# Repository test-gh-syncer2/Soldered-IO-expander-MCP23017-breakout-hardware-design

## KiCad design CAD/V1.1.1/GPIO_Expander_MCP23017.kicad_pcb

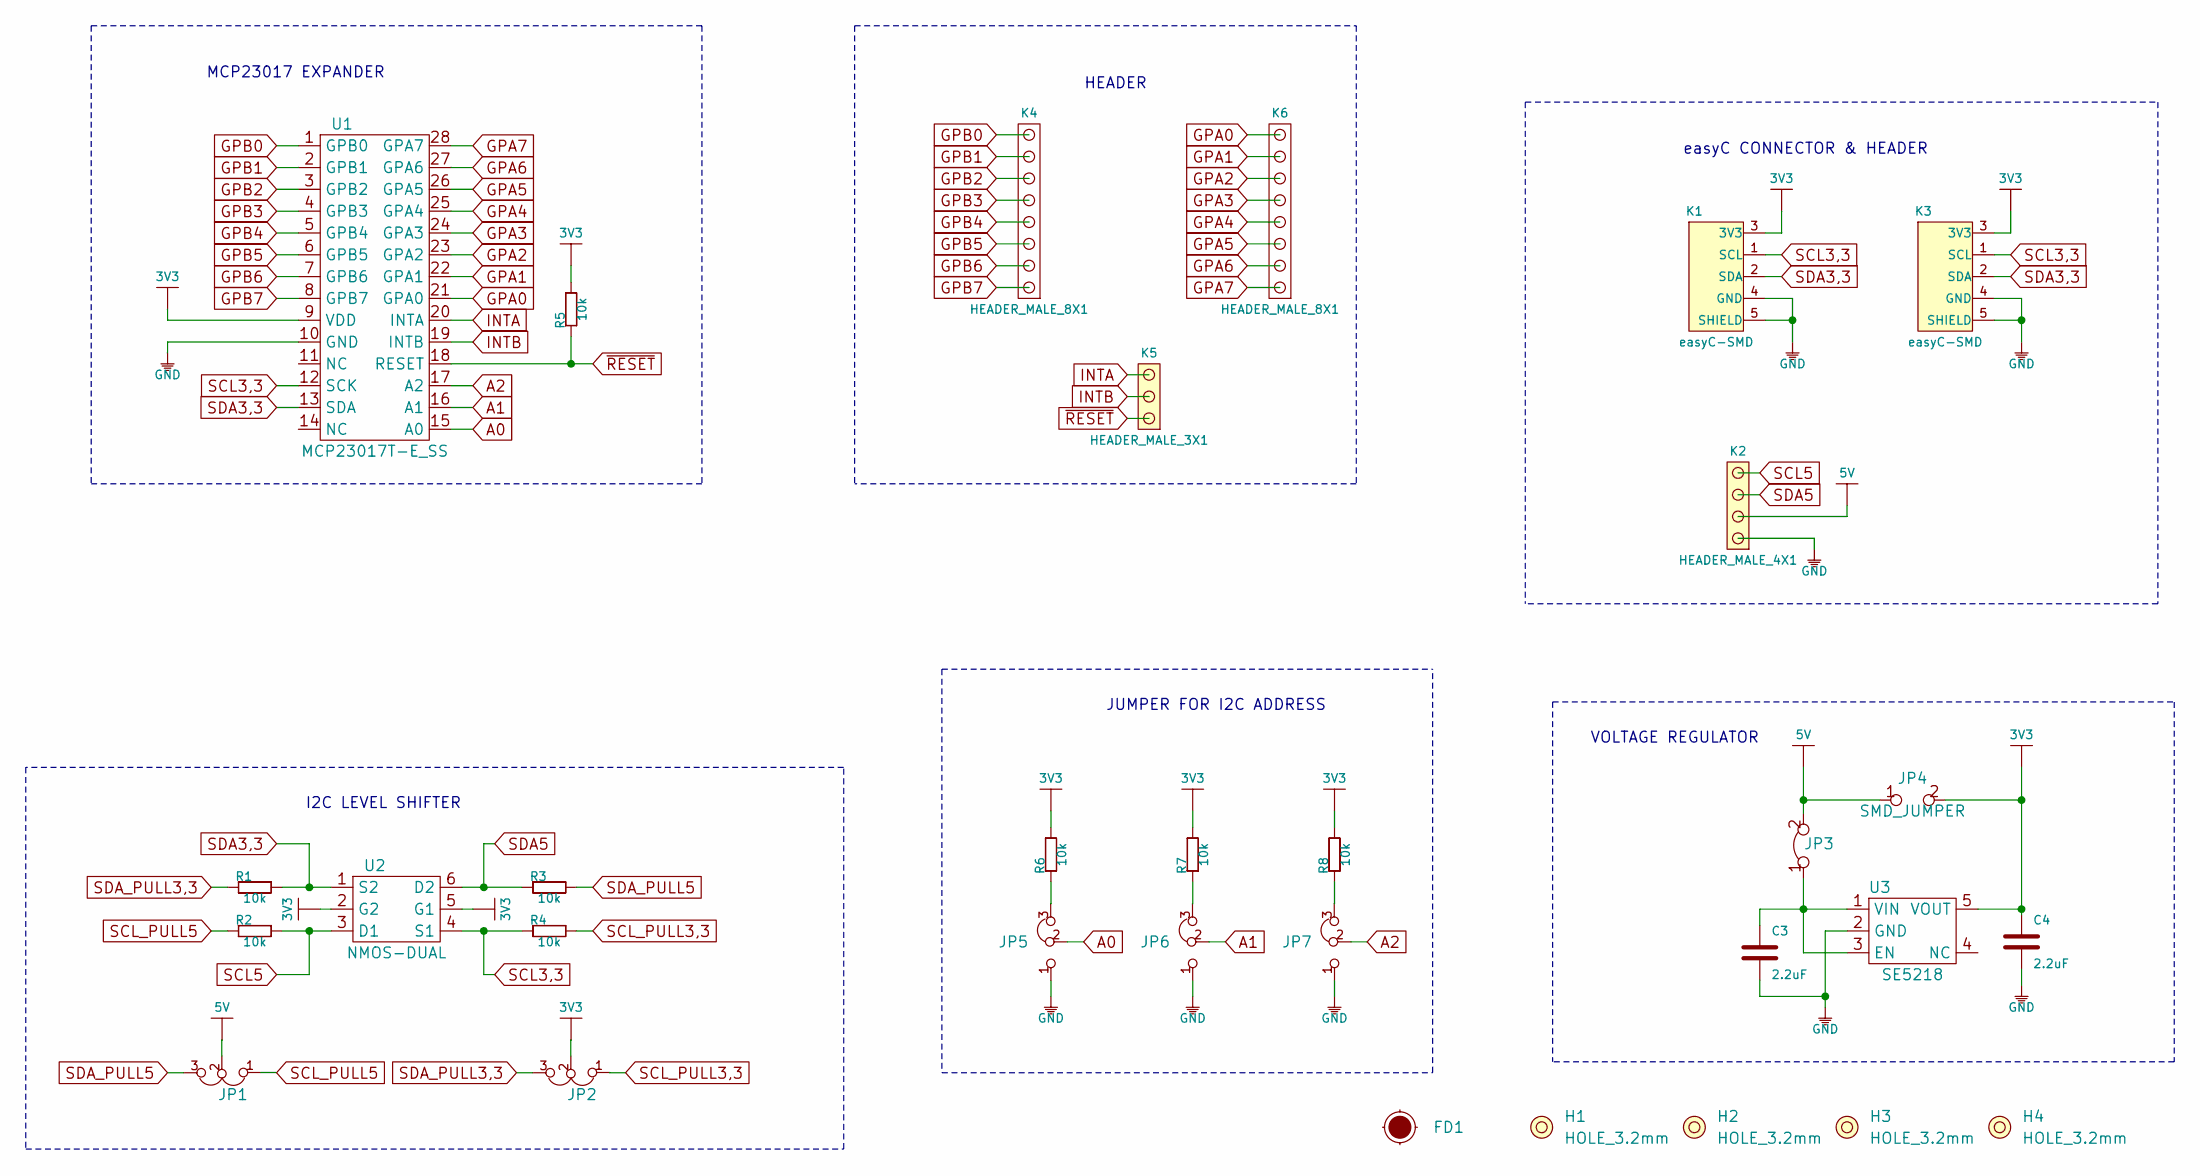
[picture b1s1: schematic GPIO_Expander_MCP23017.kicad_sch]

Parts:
C3, C4: 2.2uF; 0603C
FD1: Fiducial_Stencil; FIDUCIAL_1MM_PASTE
H1, H2, H3, H4: HOLE_3.2mm
JP1, JP2: SMD_JUMPER_3_PAD_TRACE
JP3: SMD-JUMPER-CONNECTED_TRACE_SLODERMASK
JP4: SMD_JUMPER
JP5, JP6, JP7: SMD_JUMPER_3_PAD_CONNECTED_RIGHT
K1, K3: easyC-SMD; easyC-connector
K2: HEADER_MALE_4X1
K4, K6: HEADER_MALE_8X1
K5: HEADER_MALE_3X1
R1, R2, R3, R4, R5, R6, R7, R8: 10k; 0603R
U1: MCP23017T-E_SS; MCP23017
U2: NMOS-DUAL; SOT-363
U3: SE5218; SOT-23-5

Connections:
3V3: C4.2, JP2.2, JP4.2, K1.3 (3V3), K3.3 (3V3), R5.2, R6.2, R7.2, R8.2, U1.9 (VDD), U2.2 (G2), U2.5 (G1), U3.5 (VOUT)
5V: JP1.2, JP3.2, JP4.1, K2.2
A0: JP5.2, U1.15 (A0)
A1: JP6.2, U1.16 (A1)
A2: JP7.2, U1.17 (A2)
GND: C3.1, C4.1, JP5.1, JP6.1, JP7.1, K1.4 (GND), K1.5 (SHIELD), K2.1, K3.4 (GND), K3.5 (SHIELD), U1.10 (GND), U3.2 (GND)
GPA0: K6.8, U1.21 (GPA0)
GPA1: K6.7, U1.22 (GPA1)
GPA2: K6.6, U1.23 (GPA2)
GPA3: K6.5, U1.24 (GPA3)
GPA4: K6.4, U1.25 (GPA4)
GPA5: K6.3, U1.26 (GPA5)
GPA6: K6.2, U1.27 (GPA6)
GPA7: K6.1, U1.28 (GPA7)
GPB0: K4.8, U1.1 (GPB0)
GPB1: K4.7, U1.2 (GPB1)
GPB2: K4.6, U1.3 (GPB2)
GPB3: K4.5, U1.4 (GPB3)
GPB4: K4.4, U1.5 (GPB4)
GPB5: K4.3, U1.6 (GPB5)
GPB6: K4.2, U1.7 (GPB6)
GPB7: K4.1, U1.8 (GPB7)
INTA: K5.3, U1.20 (INTA)
INTB: K5.2, U1.19 (INTB)
unnamed: C3.2, JP3.1, U3.1 (VIN), U3.3 (EN)
unnamed: JP5.3, R6.1
unnamed: JP6.3, R7.1
unnamed: JP7.3, R8.1
SCL3,3: K1.1 (SCL), K3.1 (SCL), R4.1, U1.12 (SCK), U2.4 (S1)
SCL5: K2.4, R2.2, U2.3 (D1)
SCL_PULL3,3: JP2.1, R4.2
SCL_PULL5: JP1.1, R2.1
SDA3,3: K1.2 (SDA), K3.2 (SDA), R1.2, U1.13 (SDA), U2.1 (S2)
SDA5: K2.3, R3.1, U2.6 (D2)
SDA_PULL3,3: JP2.3, R1.1
SDA_PULL5: JP1.3, R3.2
~RESET: K5.1, R5.1, U1.18 (RESET)

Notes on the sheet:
MCP23017 EXPANDER
I2C LEVEL SHIFTER
HEADER
JUMPER FOR I2C ADDRESS
VOLTAGE REGULATOR
easyC CONNECTOR & HEADER

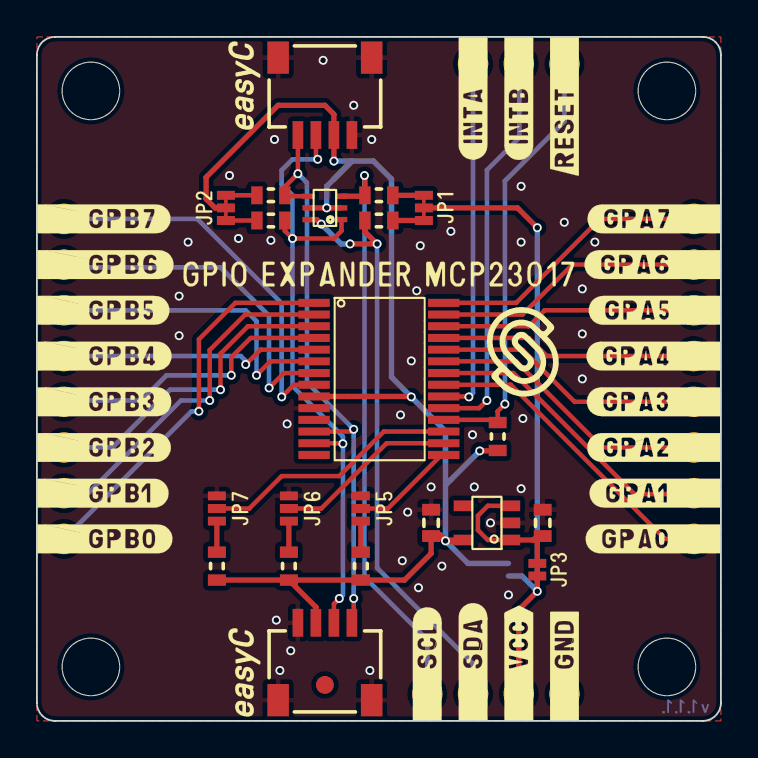
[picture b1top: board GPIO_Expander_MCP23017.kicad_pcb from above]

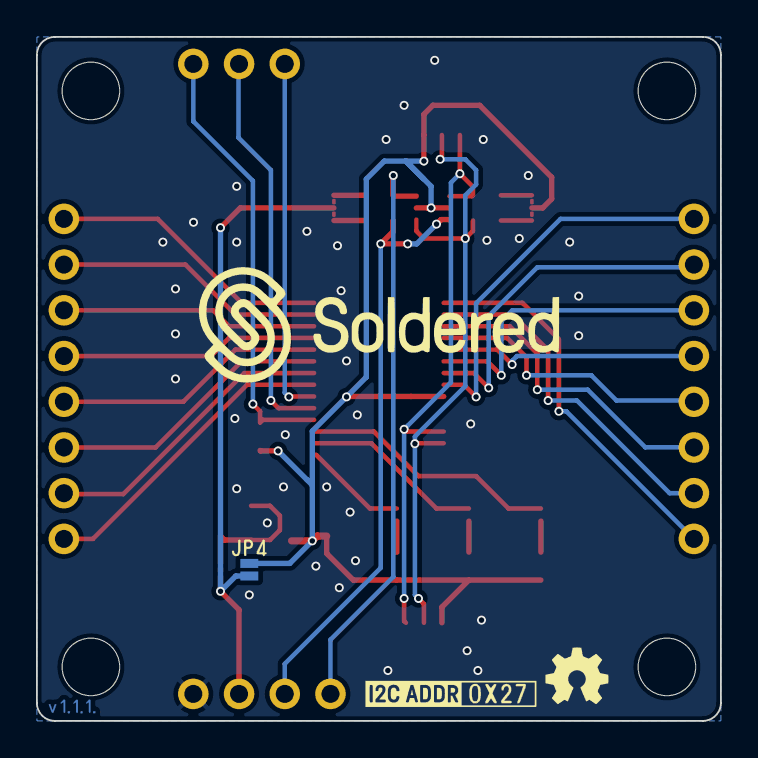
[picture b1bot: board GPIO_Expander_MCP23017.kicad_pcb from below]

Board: 2 copper layers, 38.0 x 38.0 mm, 31 parts (5 on the bottom side), 37 nets.

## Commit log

2021-09-23 Syncing to git
2021-09-23 Updating open source files.
